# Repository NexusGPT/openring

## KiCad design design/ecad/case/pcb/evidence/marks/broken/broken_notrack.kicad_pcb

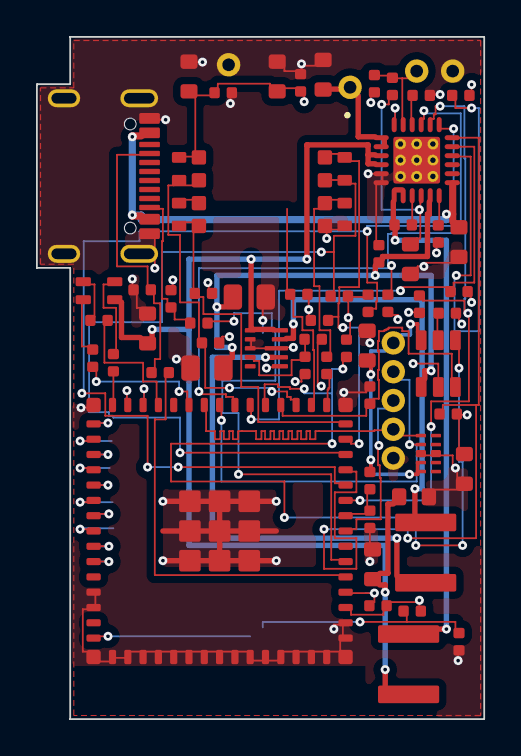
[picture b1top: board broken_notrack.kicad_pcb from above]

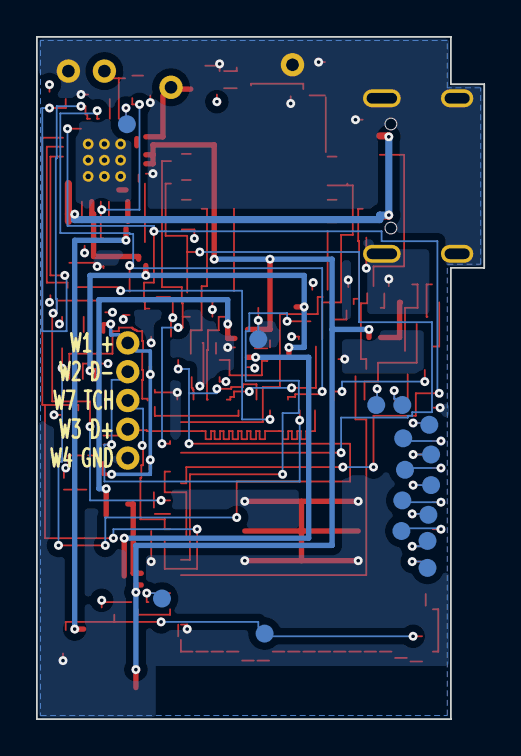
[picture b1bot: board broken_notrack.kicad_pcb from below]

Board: 4 copper layers, 24.8 x 37.9 mm, 84 parts (16 on the bottom side), 61 nets.

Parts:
BT1: 700mAh 3.7V; CELL_LEADS
C1: 1uF; SMD_0603
C2, C3: 22uF; SMD_0805
C4, C5, C6, C9, C11, C15: 10uF; SMD_0603
C7: 47nF; SMD_0402
C8: 4.7uF 10V; SMD_0603
C10, C13, C16: 100nF; SMD_0402
C12: 22uF; SMD_0603
C14: 4.7uF; SMD_0603
C30: 1uF; SMD_0402
J1: USB-C; USB4105-GF-A
L1: 1uH; L_XFL40xx_4x4
L2: 0.47uH; L_XFL40xx_4x4
LED1: RGB; LED_APTF1616
R1, R2: 5.1k; SMD_0402
R3: 511k; SMD_0402
R4: 91k; SMD_0402
R5: 59.0k; SMD_0402
R6, R7, R12, R25, R27: 100k; SMD_0402
R8: 510R; SMD_0402
R9, R10: 270R; SMD_0402
R11: 260R; SMD_0402
R13: 47k; SMD_0402
R14, R15, R16, R17, R18, R19, R20, R21, R22, R23, R24, R28, R29, R30: 10k; SMD_0402
R26: 22R; SMD_0402
RT1: 5.23k; SMD_0402
RT2: 30.1k; SMD_0402
TH1: 10k 103AT; NTC_wired
TP1, TP2, TP3, TP4, TP5, TP6, TP7, TP8, TP9, TP10, TP11, TP12, TP13, TP14, TP15, TP16: pad; TESTPAD_1.0
U1: ESP32-S3-MINI-1-N8; ESP32-S3-MINI-1
U2: BQ25895; WQFN-24_RTW_4x4
U3: TPS63802; DFN-10_DLA_2x3
U4: ZDSD64GLQEAG-R; LGA16_9x10_ZDSD
U5: TPS2553; SOT-23-6_DBV
U6: TPD4E05U06; USON-10_DQA_1x2.5
W1, W2, W3, W4, W7: wire 30AWG; WIRE_PTH_0.7
W5: cell lead +; WIRE_PTH_0.7
W6: cell lead -; WIRE_PTH_0.7

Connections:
3V3: C9.1, C10.1, C12.1, C13.1, C14.1, R3.1, R14.2, R15.2, R16.2, R17.2, R18.2, R19.2, R20.2, R21.2, R22.2, R23.2, R24.2, R28.2, R29.2, R30.2, U1.3, U3.6, U4.5
BAT: C6.1, U2.13, U2.14, W5.1
BOOT: R22.1, TP1.1, U1.4
BTST: C7.1, U2.21
CC1: J1.A5, R1.1, R6.1
CC1_SENSE: R6.2, U1.5
CC2: J1.B5, R2.1, R7.1
CC2_SENSE: R7.2, U1.6
CHG_CE_N: R21.1, U1.22, U2.9
CHG_DSEL: R28.1, U2.24
CHG_INT_N: R16.1, U1.11, U2.7
CHG_OTG: R27.1, U1.10, U2.8
CHG_STAT: R24.1, U2.4
EN: C30.1, R23.1, TP2.1, U1.45
FB: R3.2, R4.1, U3.4
GND: C1.2, C2.2, C3.2, C4.2, C5.2, C6.2, C8.2, C9.2, C10.2, C11.2, C12.2, C13.2, C14.2, C15.2, C16.2, C30.2, J1.A1, J1.A12, J1.B1, J1.B12, J1.SH, R1.2, R2.2, R4.2, R5.2, R11.2, R13.2, R25.2, R27.2, RT2.2, TH1.2, TP16.1, U1.1, U1.2, U1.42, U1.43, U1.46, U1.47, U1.48, U1.49, U1.50, U1.51, U1.52, U1.53, U1.54, U1.55, U1.56, U1.57, U1.58, U1.59, U1.60, U1.61, U1.62, U1.63, U1.64, U1.65, U2.17, U2.18, U2.25, U3.2, U3.3, U3.8, U4.4, U5.2, U6.3, U6.8, W4.1, W6.1
I2C_SCL: R15.1, U1.21, U2.5
I2C_SDA: R14.1, U1.12, U2.6
ILIM: R11.1, U2.10
LED_B: R10.1, U1.30
LED_G: R9.1, U1.27
LED_KB: LED1.4, R10.2
LED_KG: LED1.3, R9.2
LED_KR: LED1.2, R8.2
LED_R: R8.1, U1.25
PMID: C2.1, C3.1, C16.1, U2.23, U5.1
QON: TP5.1, U2.12
REGN: C8.1, RT1.1, U2.22
RING_TOUCH: U1.8, W7.1
RXD0: TP4.1, U1.40
SD_CLK: R26.1, U1.16
SD_CLK_U4: R26.2, U4.3
SD_CMD: R18.1, U1.15, U4.8
SD_D0: R19.1, U1.17, U4.7
SD_D1: R20.1, U1.18, U4.6
SD_D2: R29.1, U1.14, U4.1
SD_D3: R30.1, U1.13, U4.2
SPARE_IO33: TP6.1, U1.28
SPARE_IO34: TP7.1, U1.29
SPARE_IO35: TP8.1, U1.31
SPARE_IO36: TP9.1, U1.32
SPARE_IO37: TP10.1, U1.33
SPARE_IO38: TP11.1, U1.34
SPARE_IO39: TP12.1, U1.35
SPARE_IO40: TP13.1, U1.36
SPARE_IO41: TP14.1, U1.37
SPARE_IO42: TP15.1, U1.38
SW: C7.2, L1.1, U2.19, U2.20
SYS: C4.1, C5.1, C11.1, L1.2, LED1.1, U2.15, U2.16, U3.1, U3.10
TS: RT1.2, RT2.1, TH1.1, U2.11
TXD0: TP3.1, U1.39
U3_L1: L2.1, U3.9
U3_L2: L2.2, U3.7
U5_ILIM: R5.1, U5.5
USB_D+: U1.24, U6.1, W3.1
USB_D-: U1.23, U6.2, W2.1
VBUS_IN: C1.1, J1.A4, J1.A9, J1.B4, J1.B9, U2.1
VRING: C15.1, R12.1, U5.6, U6.4, U6.5, W1.1
VRING_EN: R25.1, U1.19, U5.3
VRING_FAULT_N: R17.1, U1.20, U5.4
VRING_SENSE: R12.2, R13.1, U1.9

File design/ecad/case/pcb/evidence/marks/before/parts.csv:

reference,symbol,value,mpn,footprint,sheet,dnp
U1,ESP32-S3-MINI-1,ESP32-S3-MINI-1-N8,ESP32-S3-MINI-1-N8,OpenRingCase:ESP32-S3-MINI-1,main,no
C9,C,10uF,GRM188R60J106ME47D,OpenRingCase:SMD_0603,main,no
C10,C,100nF,GRM155R71C104KA88D,OpenRingCase:SMD_0402,main,no
R23,R,10k,RC0402FR-0710KL,OpenRingCase:SMD_0402,main,no
C30,C,1uF,GRM155R61A105KE15D,OpenRingCase:SMD_0402,main,no
R22,R,10k,RC0402FR-0710KL,OpenRingCase:SMD_0402,main,no
R14,R,10k,RC0402FR-0710KL,OpenRingCase:SMD_0402,main,no
R15,R,10k,RC0402FR-0710KL,OpenRingCase:SMD_0402,main,no
R16,R,10k,RC0402FR-0710KL,OpenRingCase:SMD_0402,main,no
R17,R,10k,RC0402FR-0710KL,OpenRingCase:SMD_0402,main,no
R21,R,10k,RC0402FR-0710KL,OpenRingCase:SMD_0402,main,no
R25,R,100k,RC0402FR-07100KL,OpenRingCase:SMD_0402,main,no
R8,R,510R,RC0402FR-07510RL,OpenRingCase:SMD_0402,main,no
R9,R,270R,RC0402FR-07270RL,OpenRingCase:SMD_0402,main,no
R10,R,270R,RC0402FR-07270RL,OpenRingCase:SMD_0402,main,no
LED1,APTF1616,RGB,APTF1616SEEZGQBDC,OpenRingCase:LED_APTF1616,main,no
U2,BQ25895,BQ25895,BQ25895RTWR,OpenRingCase:WQFN-24_RTW_4x4,power,no
C1,C,1uF,GRM188R61A105KA61D,OpenRingCase:SMD_0603,power,no
C2,C,22uF,GRM21BR61A226ME44L,OpenRingCase:SMD_0805,power,no
C3,C,22uF,GRM21BR61A226ME44L,OpenRingCase:SMD_0805,power,no
C4,C,10uF,GRM188R61A106KE69D,OpenRingCase:SMD_0603,power,no
C5,C,10uF,GRM188R61A106KE69D,OpenRingCase:SMD_0603,power,no
C6,C,10uF,GRM188R61A106KE69D,OpenRingCase:SMD_0603,power,no
C7,C,47nF,GRM155R71C473KA01D,OpenRingCase:SMD_0402,power,no
C8,C,4.7uF 10V,GRM188R61A475KE15D,OpenRingCase:SMD_0603,power,no
L1,L,1uH,XFL4020-102MEC,OpenRingCase:L_XFL40xx_4x4,power,no
R11,R,260R,RC0402FR-07261RL,OpenRingCase:SMD_0402,power,no
RT1,R,5.23k,RC0402FR-075K23L,OpenRingCase:SMD_0402,power,no
RT2,R,30.1k,RC0402FR-0730K1L,OpenRingCase:SMD_0402,power,no
TH1,NTC,10k 103AT,103AT-2,OpenRingCase:NTC_wired,power,no
R24,R,10k,RC0402FR-0710KL,OpenRingCase:SMD_0402,power,no
R28,R,10k,RC0402FR-0710KL,OpenRingCase:SMD_0402,power,no
R27,R,100k,RC0402FR-07100KL,OpenRingCase:SMD_0402,power,no
U3,TPS63802,TPS63802,TPS63802DLAR,OpenRingCase:DFN-10_DLA_2x3,power,no
L2,L,0.47uH,XFL4015-471MEC,OpenRingCase:L_XFL40xx_4x4,power,no
R3,R,511k,RC0402FR-07511KL,OpenRingCase:SMD_0402,power,no
R4,R,91k,RC0402FR-0791KL,OpenRingCase:SMD_0402,power,no
C11,C,10uF,GRM188R61A106KE69D,OpenRingCase:SMD_0603,power,no
C12,C,22uF,GRM188R60J226MEA0D,OpenRingCase:SMD_0603,power,no
BT1,CELL,700mAh 3.7V,DNK852338,OpenRingCase:CELL_LEADS,power,no
W5,PIN1,cell lead +,,OpenRingCase:WIRE_PTH_0.7,power,no
W6,PIN1,cell lead -,,OpenRingCase:WIRE_PTH_0.7,power,no
J1,USB4105,USB-C,USB4105-GF-A,OpenRingCase:USB4105-GF-A,usbc,no
R1,R,5.1k,RC0402FR-075K1L,OpenRingCase:SMD_0402,usbc,no
R2,R,5.1k,RC0402FR-075K1L,OpenRingCase:SMD_0402,usbc,no
R6,R,100k,RC0402FR-07100KL,OpenRingCase:SMD_0402,usbc,no
R7,R,100k,RC0402FR-07100KL,OpenRingCase:SMD_0402,usbc,no
U5,TPS2553,TPS2553,TPS2553DBVR,OpenRingCase:SOT-23-6_DBV,ringlink,no
R5,R,59.0k,RC0402FR-0759KL,OpenRingCase:SMD_0402,ringlink,no
C16,C,100nF,GRM155R71C104KA88D,OpenRingCase:SMD_0402,ringlink,no
C15,C,10uF,GRM188R61A106KE69D,OpenRingCase:SMD_0603,ringlink,no
R12,R,100k,RC0402FR-07100KL,OpenRingCase:SMD_0402,ringlink,no
R13,R,47k,RC0402FR-0747KL,OpenRingCase:SMD_0402,ringlink,no
U6,TPD4E05U06,TPD4E05U06,TPD4E05U06DQAR,OpenRingCase:USON-10_DQA_1x2.5,ringlink,no
P1,PIN1,spring pin,P70-6000045R,OpenRingCase:HARWIN_P70_6000045R,ringlink,no
W1,PIN1,wire 30AWG,,OpenRingCase:WIRE_PTH_0.7,ringlink,no
P2,PIN1,spring pin,P70-6000045R,OpenRingCase:HARWIN_P70_6000045R,ringlink,no
W2,PIN1,wire 30AWG,,OpenRingCase:WIRE_PTH_0.7,ringlink,no
P3,PIN1,spring pin,P70-6000045R,OpenRingCase:HARWIN_P70_6000045R,ringlink,no
W3,PIN1,wire 30AWG,,OpenRingCase:WIRE_PTH_0.7,ringlink,no
P4,PIN1,spring pin,P70-6000045R,OpenRingCase:HARWIN_P70_6000045R,ringlink,no
W4,PIN1,wire 30AWG,,OpenRingCase:WIRE_PTH_0.7,ringlink,no
E1,PIN1,touch electrode 6x3,,OpenRingCase:TOUCH_E1_front,ringlink,no
W7,PIN1,wire 30AWG,,OpenRingCase:WIRE_PTH_0.7,ringlink,no
U4,ZDSD64GLQEAG,ZDSD64GLQEAG-R,ZDSD64GLQEAG-R,OpenRingCase:LGA16_9x10_ZDSD,storage,no
R26,R,22R,RC0402FR-0722RL,OpenRingCase:SMD_0402,storage,no
R18,R,10k,RC0402FR-0710KL,OpenRingCase:SMD_0402,storage,no
R19,R,10k,RC0402FR-0710KL,OpenRingCase:SMD_0402,storage,no
R20,R,10k,RC0402FR-0710KL,OpenRingCase:SMD_0402,storage,no
R29,R,10k,RC0402FR-0710KL,OpenRingCase:SMD_0402,storage,no
R30,R,10k,RC0402FR-0710KL,OpenRingCase:SMD_0402,storage,no
C13,C,100nF,GRM155R71C104KA88D,OpenRingCase:SMD_0402,storage,no
C14,C,4.7uF,GRM188R61A475KE15D,OpenRingCase:SMD_0603,storage,no
TP1,PIN1,pad,,OpenRingCase:TESTPAD_1.0,test,no
TP2,PIN1,pad,,OpenRingCase:TESTPAD_1.0,test,no
TP3,PIN1,pad,,OpenRingCase:TESTPAD_1.0,test,no
TP4,PIN1,pad,,OpenRingCase:TESTPAD_1.0,test,no
TP5,PIN1,pad,,OpenRingCase:TESTPAD_1.0,test,no
TP6,PIN1,pad,,OpenRingCase:TESTPAD_1.0,test,no
TP7,PIN1,pad,,OpenRingCase:TESTPAD_1.0,test,no
TP8,PIN1,pad,,OpenRingCase:TESTPAD_1.0,test,no
TP9,PIN1,pad,,OpenRingCase:TESTPAD_1.0,test,no
TP10,PIN1,pad,,OpenRingCase:TESTPAD_1.0,test,no
TP11,PIN1,pad,,OpenRingCase:TESTPAD_1.0,test,no
TP12,PIN1,pad,,OpenRingCase:TESTPAD_1.0,test,no
TP13,PIN1,pad,,OpenRingCase:TESTPAD_1.0,test,no
TP14,PIN1,pad,,OpenRingCase:TESTPAD_1.0,test,no
TP15,PIN1,pad,,OpenRingCase:TESTPAD_1.0,test,no
TP16,PIN1,pad,,OpenRingCase:TESTPAD_1.0,test,no

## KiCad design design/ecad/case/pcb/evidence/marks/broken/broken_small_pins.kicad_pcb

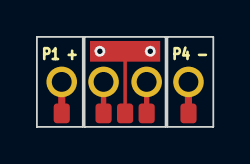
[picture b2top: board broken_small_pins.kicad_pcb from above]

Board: 2 copper layers, 9.8 x 5.0 mm, 10 parts (0 on the bottom side), 5 nets.

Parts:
E1: touch electrode 6x3; TOUCH_E1_front
P1, P2, P3, P4: spring pin; HARWIN_P70_6000045R
WP1: wire 30AWG pin-board end of W1; WIRE_SMD_0.9x1.1
WP2: wire 30AWG pin-board end of W2; WIRE_SMD_0.9x1.1
WP3: wire 30AWG pin-board end of W3; WIRE_SMD_0.9x1.1
WP4: wire 30AWG pin-board end of W4; WIRE_SMD_0.9x1.1
WP7: wire 30AWG pin-board end of W7; WIRE_SMD_0.9x1.1

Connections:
GND: P4.1, WP4.1
RING_TOUCH: E1.1, WP7.1
USB_D+: P3.1, WP3.1
USB_D-: P2.1, WP2.1
VRING: P1.1, WP1.1

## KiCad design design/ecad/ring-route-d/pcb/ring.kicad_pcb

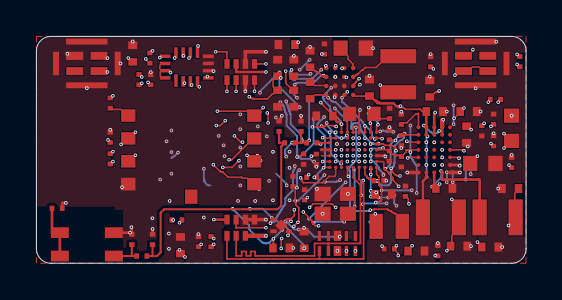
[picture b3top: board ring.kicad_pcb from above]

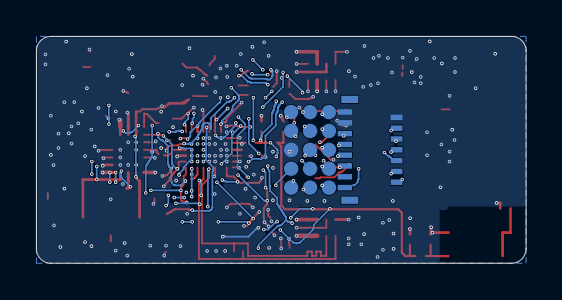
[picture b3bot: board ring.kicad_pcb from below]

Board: 4 copper layers, 27.2 x 12.6 mm, 100 parts (16 on the bottom side), 87 nets.

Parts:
ANT1: 2450AT18D0100001E; ANT_Johanson_2450AT18D0100001E_3.2x1.6
C1, C2, C5, C61, C72, C80, C81, C82: 100nF; Chip_0201
C3: 1.2pF; Chip_0201
C4, C22, C25, C74, C75, C78, C79, C83, C84: 10uF; Chip_0402
C6: 4.7uF; Chip_0201
C7, C10, C14: 2.2uF; Chip_0201
C11, C21, C26, C27: 4.7uF; Chip_0402
C12: 0.5pF; Chip_0201
C13, C89: DNP; Chip_0201
C23, C60, C85: 2.2uF; Chip_0402
C24, C88: 10uF; Chip_0603
C28, C29: 22uF; Chip_0402
C31, C32: 1uF; Chip_0201
C35, C36: 1nF C0G; Chip_0402
C71: 1.0uF 25V; Chip_0402
C73: 1.0uF; Chip_0201
C76, C77: 1.0nF; Chip_0201
C86, C87: 1.0uF; Chip_0402
FB1: 120R@100MHz; Chip_0201
J1: FH35C-15S-0.3SHW(50); FPC_Hirose_FH35C-15S-0.3SHW
J_BAND_A: flex tail A (joystick side) 8 pads; J_BAND_A_BOARD
J_BAND_B: flex tail B (other side) 7 pads; J_BAND_B_BOARD
L1: 4.7uH; L_TDK_MLZ1608_1.6x0.8
L2: 3.6nH; Chip_0201
L3: 4.7nH; Chip_0201
L4: 3.3nH; Chip_0201
L10, L71, L72: 2.2uH; L_Murata_1269AS-H_2.5x2.0
LT1: 0R; Chip_0201
R1: 2.2R; Chip_0603
R2: 220R; Chip_0201
R31, R32, R61: 100R; Chip_0201
R57, R58: 4.7k; Chip_0201
R60, R63, R64, R65, R71: 47k; Chip_0201
R62, R66: 100k; Chip_0201
R72: 150k; Chip_0201
TP1, TP3, TP4, TP5, TP6, TP8, TP9, TP11, TP12, TP14, TP15, TP17, TP18, TP19, TP21: pad; TESTPAD_0.8
U1: nRF54LM20A; WLCSP-61_nRF54LM20A-CAAA
U2: nPM1304; WLCSP-35_nPM1304-CAAA
U3: CSNP32GCR01-BOW; LGA-9_CSNP32GCR01-BOW_8.0x6.2
U4: SGM38046; WLCSP-16_SGM38046_2.0x2.0_P0.5
U5, U6: SPK0641HT4H-1; LGA-8_Knowles_SPK0641HT4H-1_3.0x4.0
U9: TPD4E05U06; USON-10_TPD4E05U06DQA
U10: SN74AXC4T774; UQFN-16_SN74AXC4T774RSV_1.8x2.6
U11: TLV75530P 3.0V; X2SON-4_TLV755xxPDQN_1.0x1.0
X1: 32MHz; XTAL_Kyocera_CX2016DB_2.0x1.6
X2: 32.768kHz; XTAL_TXC_9HT11_2.0x1.2

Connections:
ANT1_NODE: L2.1, U1.C1
ANT2_NODE: C3.1, L2.2, L3.1
ANT3_NODE: C12.1, C89.1, L3.2, L4.1
ANT_TRIM: ANT1.2, ANT1.3, LT1.1
BTN_REC: J_BAND_A.5, U1.H2
DBG_TX: TP1.1, U1.B4
DCC: L1.1, U1.A5
DECA: C7.1, C14.1, FB1.2, U1.A8, U1.B2
DECD: C6.1, FB1.1, L1.2, U1.A6
ELVDD: C25.1, J1.2, U4.D3
ELVSS: C28.1, C29.1, J1.1, U4.D4
GND: ANT1.4, C1.2, C2.2, C3.2, C4.2, C5.2, C6.2, C7.2, C10.2, C11.2, C12.2, C13.2, C14.2, C21.2, C22.2, C24.2, C25.2, C26.2, C27.2, C28.2, C29.2, C31.2, C32.2, C35.2, C36.2, C60.2, C61.2, C71.2, C72.2, C73.2, C74.2, C75.2, C76.2, C77.2, C78.2, C79.2, C80.2, C81.2, C82.2, C83.2, C84.2, C85.2, C86.2, C87.2, C88.2, C89.2, J1.13, J1.14, J1.15, J_BAND_A.6, J_BAND_A.8, J_BAND_B.2, J_BAND_B.7, LT1.2, R2.2, R62.2, R66.2, R71.2, R72.2, TP18.1, U1.A7, U1.D3, U1.E1, U1.F10, U2.A6, U2.A7, U2.E7, U3.4, U4.A3, U4.B2, U4.B3, U5.3, U5.5, U5.6, U5.7, U5.8, U6.5, U6.6, U6.7, U6.8, U9.3, U9.8, U10.6, U10.7, U10.8, U11.2, U11.5, X1.2
JOY_DOWN: J_BAND_A.2, U1.G2
JOY_LEFT: J_BAND_A.3, U1.G1
JOY_RIGHT: J_BAND_A.4, U1.G10
JOY_UP: J_BAND_A.1, U1.H1
LCD_CS: J1.9, U1.F7
LCD_DCX: J1.11, U1.G7
LCD_MOSI: J1.12, U1.G8
LCD_RST: J1.8, U1.H5
LCD_SCK: J1.10, U1.G9
LCD_TE: J1.7, U1.D6
MIC1_DATA: R31.1, U5.1
MIC2_DATA: R32.1, U6.1
MIC_A_CLK: U1.F1, U5.2, U6.2
MIC_A_DATA: R31.2, R32.2, U1.F2
MIC_B_DATA: TP21.1, U1.D7
MOTOR: R61.1, U1.F6
MOT_EN: R61.2, R62.1, U11.3
NRESET: TP5.1, U1.E2
NTC: J_BAND_B.3, U2.D3
OLED_PWR_EN: R66.1, U1.E9, U4.C2
PMIC_INT: U1.D8, U2.D6
PMIC_SCL: R58.1, U1.E7, U2.E3
PMIC_SDA: R57.1, U1.B8, U2.E5
RF_FEED: ANT1.1, C13.1, L4.2
SDC_CS: R65.1, U3.2, U10.10
SDC_MISO: R60.1, U3.6, U10.9
SDC_MOSI: U3.5, U10.11
SDC_SCK: U3.3, U10.12
SD_CS: U1.D9, U10.3
SD_DAT1: R63.1, U3.7
SD_DAT2: R64.1, U3.1
SD_MISO: U1.D10, U10.4
SD_MOSI: U1.B10, U10.2
SD_SCK: U1.A9, U10.1
SGM_AVDD: C26.1, U4.D2
SGM_AVIN: C22.1, U4.A2
SGM_C1N: C23.2, U4.B4
SGM_C1P: C23.1, U4.A4
SGM_SW1: L10.1, U4.B1
SGM_SW2: L10.2, U4.C1
SGM_VON: C27.1, U4.C4
SGM_VOUT: C24.1, U4.D1
SHPHLD: TP19.1, U2.D4
SPARE_P1_00: TP6.1, U1.H10
SPARE_P1_02: TP8.1, U1.F8
SPARE_P1_14: TP9.1, U1.F4
SPARE_P1_30: TP11.1, U1.F9
SPARE_P2_00: TP12.1, U1.A10
SPARE_P3_03: TP14.1, U1.F5
SPARE_P3_04: TP15.1, U1.G5
SW1: L71.1, U2.B7
SW2: L72.1, U2.D7
SWDCLK: TP3.1, U1.D5
SWDIO: TP4.1, U1.E4
SWIRE: J1.6, U4.C3
TXRTUNE: R2.1, U1.G6
U1_VBUS: C11.1, R1.2, U1.H9
USB_DN: J_BAND_B.5, U1.H6, U9.2
USB_DP: J_BAND_B.6, U1.H7, U9.1
VBAT: C21.1, C83.1, C85.1, J_BAND_B.1, U2.D1, U2.D2, U4.A1, U11.4
VBUS: C71.1, C72.1, J_BAND_B.4, R1.1, U2.B1, U2.B2, U9.4, U9.5
VBUSOUT: C73.1, U2.C3
VDD_1V8: C1.1, C2.1, C4.1, C5.1, C78.1, C80.1, C81.1, J1.5, L71.2, R57.2, R58.2, TP17.1, U1.A4, U1.E10, U2.B4, U2.B6, U2.E4, U10.5, U10.14, U10.15, U10.16
VDD_3V0: C79.1, J1.4, L72.2, U2.B5, U2.C6
VDD_MIC: C31.1, C32.1, C35.1, C36.1, C86.1, U2.A4, U5.4, U6.3, U6.4
VDD_SD: C60.1, C61.1, C82.1, C87.1, R60.2, R63.2, R64.2, R65.2, U2.A5, U3.8, U10.13
VDD_USB_3V3: C10.1, U1.H8
VMOT: C84.1, J_BAND_A.7, U11.1
VSET1: R71.1, U2.E2
VSET2: R72.1, U2.E1
VSYS: C74.1, C75.1, C76.1, C77.1, C88.1, U2.C1, U2.C2, U2.C7
XC1: U1.A2, X1.1
XC2: U1.A1, X1.3
XL1: U1.B6, X2.1
XL2: U1.B7, X2.2
